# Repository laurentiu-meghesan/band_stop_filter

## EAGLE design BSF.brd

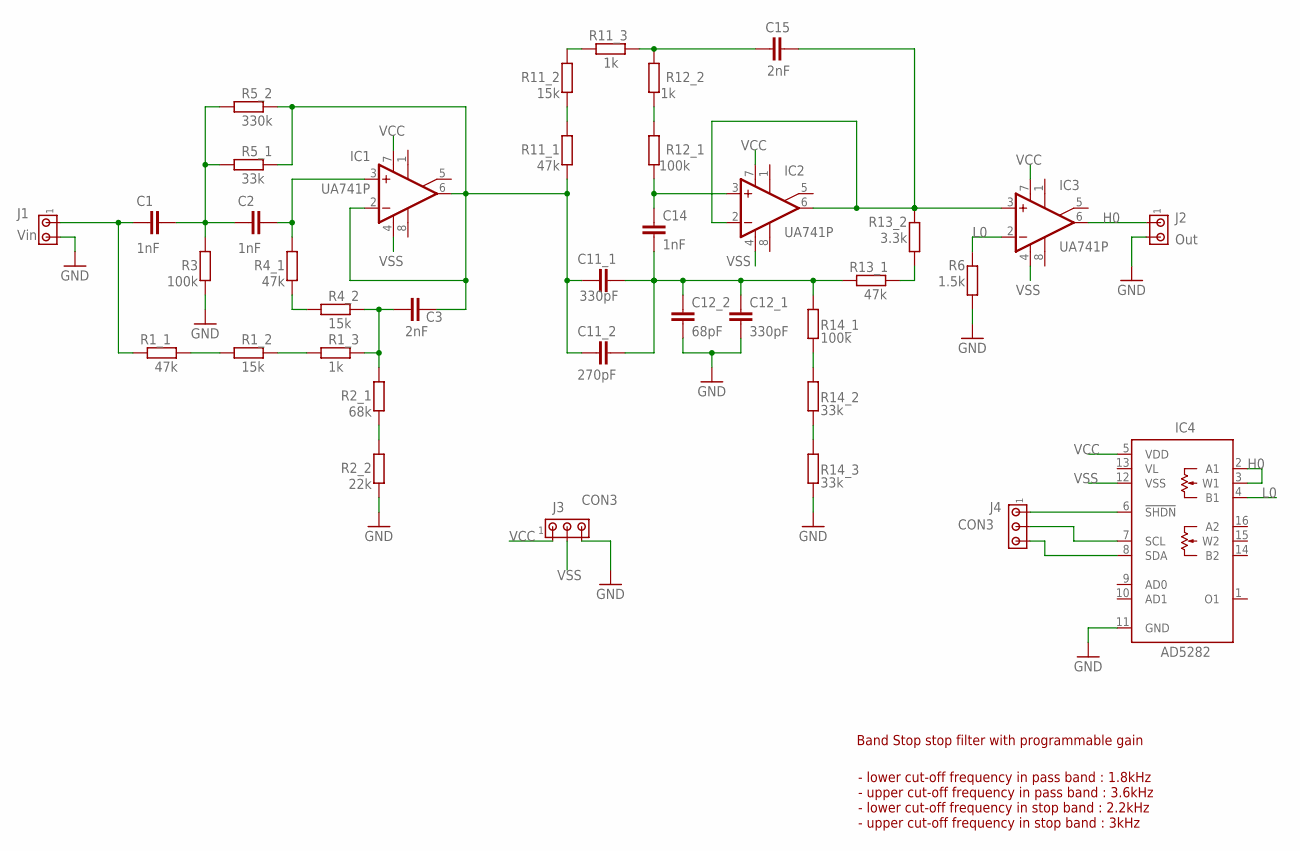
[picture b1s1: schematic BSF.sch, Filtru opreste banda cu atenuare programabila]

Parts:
C1, C2, C14: 1nF; C0805
C3, C15: 2nF; C0805
C11_1, C12_1: 330pF; C0805
C11_2: 270pF; C0805
C12_2: 68pF; C0805
IC1, IC2, IC3: UA741P; DIL08
IC4: AD5282; TSSOP16
J1: Vin; 1X2MTA
J2: Out; 1X2MTA
J3, J4: CON3; 1X3MTA
R1_1, R4_1, R11_1, R13_1: 47k; R0805
R1_2, R4_2, R11_2: 15k; R0805
R1_3, R11_3, R12_2: 1k; R0805
R2_1: 68k; R0805
R2_2: 22k; R0805
R3, R12_1, R14_1: 100k; R0805
R5_1, R14_2, R14_3: 33k; R0805
R5_2: 330k; R0805
R6: 1.5k; R0805
R13_2: 3.3k; R0805

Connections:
GND: C12_1.2, C12_2.2, IC4.11 (GND), J1.2, J2.2, J3.3, R2_2.1, R3.1, R6.1, R14_3.2
H0: IC3.6 (OUT), IC4.2 (A1), IC4.3 (W1), J2.1
L0: IC3.2 (-IN), IC4.4 (B1), R6.2
unnamed: C15.1, R11_3.2, R12_2.2
unnamed: C1.1, J1.1, R1_1.1
unnamed: C1.2, C2.1, R3.2, R5_1.1, R5_2.1
unnamed: R1_1.2, R1_2.1
unnamed: R1_2.2, R1_3.1
unnamed: R4_1.1, R4_2.1
unnamed: C2.2, IC1.3 (+IN), R4_1.2
unnamed: C3.1, R1_3.2, R2_1.2, R4_2.2
unnamed: R2_1.1, R2_2.2
unnamed: IC4.6 (!SHDN), J4.1
unnamed: IC4.7 (SCL), J4.2
unnamed: IC4.8 (SDA), J4.3
unnamed: R11_2.2, R11_3.1
unnamed: C3.2, C11_1.1, C11_2.1, IC1.2 (-IN), IC1.6 (OUT), R5_1.2, R5_2.2, R11_1.1
unnamed: R11_1.2, R11_2.1
unnamed: R12_1.2, R12_2.1
unnamed: C14.1, IC2.3 (+IN), R12_1.1
unnamed: C11_1.2, C11_2.2, C12_1.1, C12_2.1, C14.2, R13_1.1, R14_1.1
unnamed: R14_1.2, R14_2.1
unnamed: R14_2.2, R14_3.1
unnamed: C15.2, IC2.2 (-IN), IC2.6 (OUT), IC3.3 (+IN), R13_2.2
unnamed: R13_1.2, R13_2.1
VCC: IC1.7 (V+), IC2.7 (V+), IC3.7 (V+), IC4.5 (VDD), J3.1
VL: IC4.13 (VL)
VSS: IC1.4 (V-), IC2.4 (V-), IC3.4 (V-), IC4.12 (VSS), J3.2

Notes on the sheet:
Band Stop stop filter with programmable gain
- lower cut-off frequency in pass band : 1.8kHz - upper cut-off frequency in pass band : 3.6kHz - lower cut-off frequency in stop band : 2.2kHz - upper cut-off frequency in stop band : 3kHz

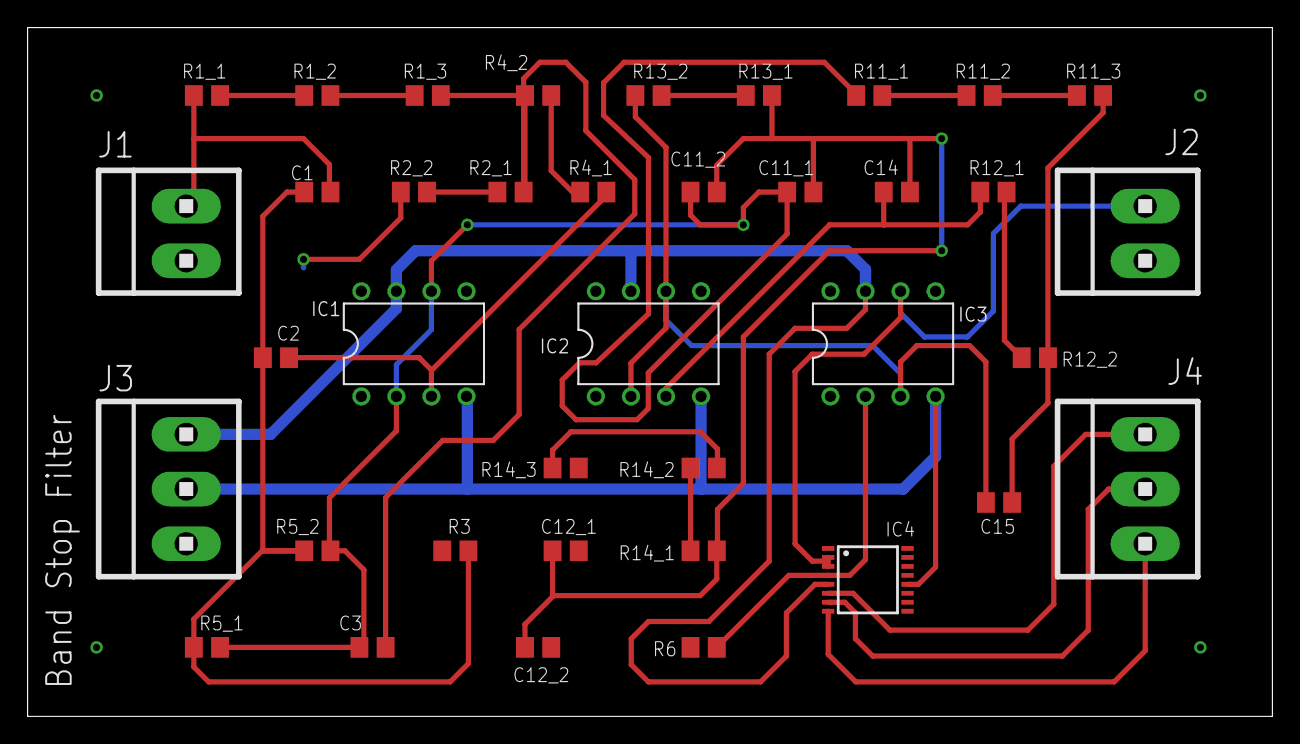
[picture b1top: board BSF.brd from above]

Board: 2 copper layers, 90.2 x 49.9 mm, 38 parts (0 on the bottom side), 27 nets.

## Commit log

2022-03-19 Band stop filter design
2022-03-21 added read me file
